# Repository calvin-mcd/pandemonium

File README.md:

# Pandemonium
 
Pandemonium is an alpha staggered ISO pcb with KLE by HaiZeus. It uses an [XIAO nRF52840](https://www.seeedstudio.com/Seeed-XIAO-BLE-nRF52840-p-5201.html) for bluetooth support. The desgin for that is based on [NoahK#1290's](https://kiserdesigns.bigcartel.com/) [Asymptote](https://github.com/KiserDesigns/Asymptote). For a build guide you can mostly refer to the steps from the [Asymptote Guide](https://github.com/KiserDesigns/Asymptote#asymptote-build-guide). Just take extra care with the right orientation of the diodes, as these change quite a bit on this pcb design. The battery cutout is 54mm x 14mm (max width for batteries used is 14mm).

## Layout

[Link](http://www.keyboard-layout-editor.com/#/gists/b0a595a186fab9d96212efed305105f0)

## Cases

1) HaiZeus designed the case to be either used for resin or FDM printing. Use the respective top file for that. 

A universal plate file is included as well as two thick plate options for different bottomrow layouts.  

Hardware needed to assemble the cases is:
- 8x M3x4mm heat set inserts or 8x M3 square nuts (depending on case top printing method) (see reference picture below for the kind of square nuts)
- 8x M3x6mm screws

The bottom has cutouts for SKUF rubber feet available at a couple different online retailers.

2) There is now also a Hull Style Case made by Ty-Fitz for the OG pandenonium pcb.
https://github.com/Ty-Fitz/Pandi-hull

## Firmware

Firmware has been created in zmk by Falconloft. A basic layout to flash the pcb has been provided. The source code is there to edit and create personal layouts for the board.

## Todo

- [X] order & test pcb
- [X] print & test case
- [X] create ZMK firmware

## Disclaimer

This PCB has been fully tested and confirmed to work. The members of the PCB development team are however not liable if you end up with a non-functional pcb. Order at your own risk. Support will not be provided but pull requests will be reviewed and possibly accepted.

## License

This project is released under the GPL v3 License. Please refer to the LICENCE file.

## Credits

Thanks to HaiZeus for the inspiration, KLE and case design.

Many thanks to Falconloft for his work and patience with the firmware.

Big, big thanks to NoahK#1290 for the design inspiration and support. Do check out Noah's work. It is amazing!

And, as always big thanks to the 40s community!

Any questions, contact calvin0563 on Discord.

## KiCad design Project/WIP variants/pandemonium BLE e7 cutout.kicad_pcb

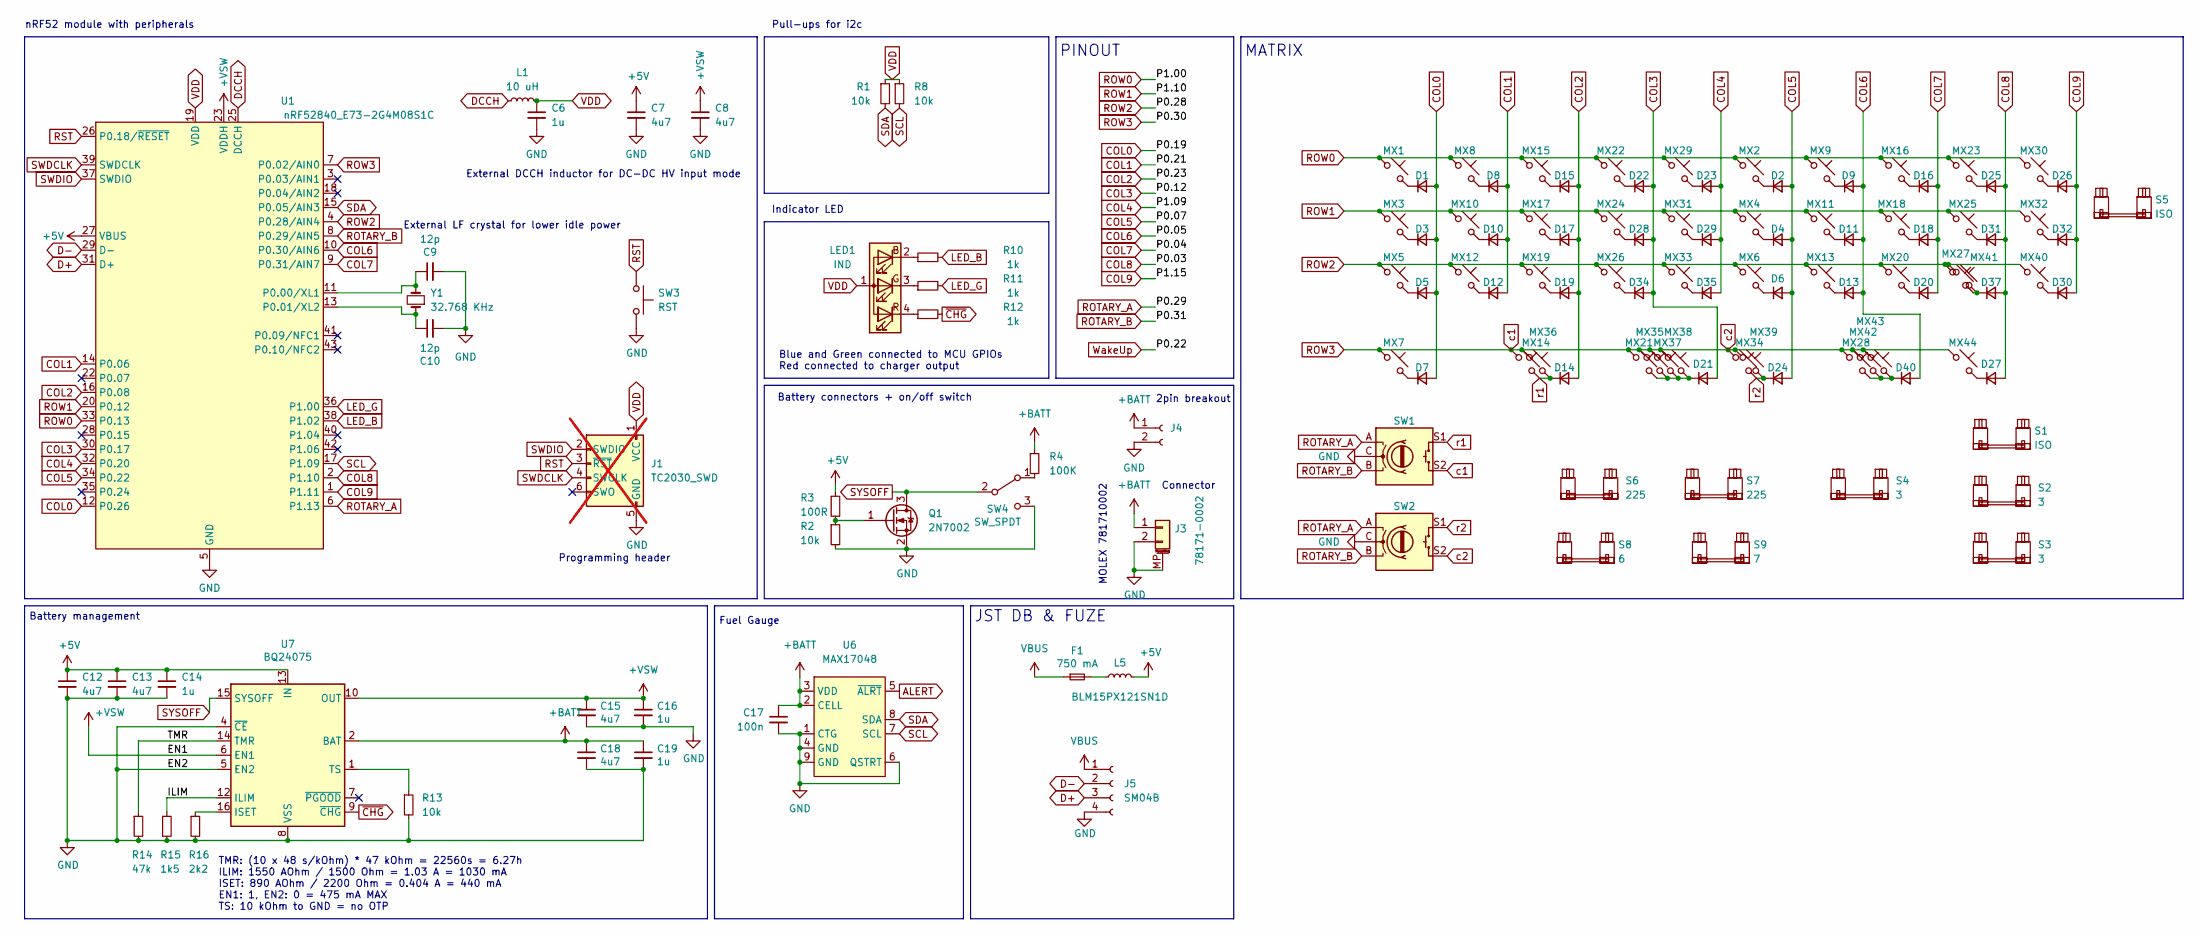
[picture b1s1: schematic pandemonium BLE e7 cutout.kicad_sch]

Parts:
C6, C14, C16, C19: 1u; C_0402_1005Metric; LCSC C52923
C7, C8, C12, C13, C15, C18: 4u7; C_0402_1005Metric; LCSC C23733
C9, C10: 12p; C_0402_1005Metric; LCSC C1547
C17: 100n; C_0402_1005Metric; LCSC C307331
D1, D2, D3, D4, D5, D6, D7, D8, D9, D10, D11, D12, D13, D14, D15, D16, D17, D18, D19, D20, D21, D22, D23, D24, D25, D26, D27, D28, D29, D30, D31, D32, D34, D35, D37, D40: D_Small; D_SOD-123F
F1: 750 mA; Fuse_1206_3216Metric; LCSC C20792
J1: TC2030_SWD; CON_TC2030_outlined; not fitted
J3: 78171-0002; Molex_Pico-EZmate_78171-0002_1x02-1MP_P1.20mm_Vertical; LCSC C505023
J4: Conn_01x02_Female; JST_PH_S2B-PH-K_1x02_P2.00mm_Horizontal
J5: SM04B; JST_SH_SM04B-SRSS-TB_1x04-1MP_P1.00mm_Horizontal
L1: 10 uH; L_0603_1608Metric; LCSC C92982
L5: BLM15PX121SN1D; L_0402_1005Metric; LCSC C88970
LED1: IND; LED_1206R; LCSC C2802677
MX1, MX2, MX3, MX4, MX6, MX8, MX9, MX10, MX11, MX12, MX13, MX14, MX15, MX16, MX17, MX18, MX19, MX20, MX21, MX22, MX23, MX24, MX25, MX26, MX27, MX28, MX29, MX30, MX31, MX32, MX33, MX34, MX35, MX37, MX39, MX42: MX_SW_solder; SW_MX_1u
MX5, MX41: MX_SW_solder; SW_MX_1.5u
MX7, MX36, MX40, MX44: MX_SW_solder; SW_MX_1.25u
MX38, MX43: MX_SW_solder; SW_MX_1.75u
Q1: 2N7002; SOT-23
R1, R8, R13: 10k; R_0402_1005Metric; LCSC C25744
R2: 10k; R_0402_1005Metric
R3: 100R; R_0402_1005Metric
R4: 100K; R_0402_1005Metric
R10, R11, R12: 1k; R_0402_1005Metric; LCSC C11702
R14: 47k; R_0402_1005Metric; LCSC C25792
R15: 1k5; R_0402_1005Metric; LCSC C25867
R16: 2k2; R_0402_1005Metric; LCSC C25879
S1: ISO; STAB_MX_P_ISO
S2, S3, S4: 3; STAB_MX_P_3u
S5: ISO; STAB_MX_P_ISO-ROT
S6, S7: 225; STAB_MX_P_2.25u
S8: 6; STAB_MX_P_6u
S9: 7; STAB_MX_P_7u
SW1, SW2: RotaryEncoder_Switch; ROT_Alps_EC11E-Switch
SW3: RST; SW_T1A2QR; LCSC C100056
SW4: SW_SPDT; SW_MSK12C02-HB
U1: nRF52840_E73-2G4M08S1C; LCSC C356849
U6: MAX17048; DFN-8-1EP_2x2mm_P0.5mm_EP0.8x1.6mm; LCSC C2682616
U7: BQ24075; VQFN-16-1EP_3x3mm_P0.5mm_EP1.6x1.6mm; LCSC C15464
Y1: 32.768 KHz; Crystal_SMD_2012-2Pin_2.0x1.2mm; LCSC C55208

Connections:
+5V: C7.1, C12.1, C13.1, C14.1, R3.1, U1.27 (VBUS), U7.13 (IN); also elsewhere on the board
+BATT: C17.1, C18.1, C19.1, J3.1, J4.1, R4.1, U6.2 (CELL), U6.3 (VDD), U7.2 (BAT), U7.3 (BAT)
+VSW: C8.1, C15.1, C16.1, U1.23 (VDDH), U7.6 (EN1), U7.10 (OUT), U7.11 (OUT)
/ILIM: R15.1, U7.12 (ILIM)
/TMR: R14.1, U7.14 (TMR)
ALERT: U6.5 (~ALRT)
COL0: D1.2 (A), D3.2 (A), D5.2 (A), D7.2 (A), U1.12 (P0.26)
COL1: D8.2 (A), D10.2 (A), D12.2 (A), U1.14 (P0.06)
COL2: D14.2 (A), D15.2 (A), D17.2 (A), D19.2 (A), U1.16 (P0.08)
COL3: D21.2 (A), D22.2 (A), D28.2 (A), D34.2 (A), U1.30 (P0.17)
COL4: D23.2 (A), D29.2 (A), D35.2 (A), U1.32 (P0.20)
COL5: D2.2 (A), D4.2 (A), D6.2 (A), D24.2 (A), U1.34 (P0.22)
COL6: D9.2 (A), D11.2 (A), D13.2 (A), D40.2 (A), U1.10 (P0.30/AIN6)
COL7: D16.2 (A), D18.2 (A), D20.2 (A), U1.9 (P0.31/AIN7)
COL8: D25.2 (A), D27.2 (A), D31.2 (A), D37.2 (A), U1.2 (P1.10)
COL9: D26.2 (A), D30.2 (A), D32.2 (A), U1.1 (P1.11)
D+: J5.3, U1.31 (D+)
D-: J5.2, U1.29 (D-)
DCCH: L1.1, U1.25 (DCCH)
GND: C6.2, C7.2, C8.2, C9.2, C10.2, C12.2, C13.2, C14.2, C15.2, C16.2, C17.2, C18.2, C19.2, J1.5 (GND), J3.2, J3.MP (MountPin), J4.2, J5.4, Q1.2 (S), R2.2, R13.2, R14.2, R15.2, R16.2, SW1.C, SW2.C, SW3.2, SW4.3 (C), U1.5 (GND), U1.21 (GND), U1.24 (GND), U6.1 (CTG), U6.4 (GND), U6.6 (QSTRT), U6.9 (GND), U7.4 (~CE), U7.5 (EN2), U7.8 (VSS), U7.17 (VSS)
LED_B: R10.2, U1.38 (P1.02)
LED_G: R11.2, U1.36 (P1.00)
unnamed: D1.1 (K), MX1.2
unnamed: D2.1 (K), MX2.2
unnamed: D3.1 (K), MX3.2
unnamed: D4.1 (K), MX4.2
unnamed: D5.1 (K), MX5.2
unnamed: D6.1 (K), MX6.2
unnamed: D7.1 (K), MX7.2
unnamed: D8.1 (K), MX8.2
unnamed: D9.1 (K), MX9.2
unnamed: D10.1 (K), MX10.2
unnamed: D11.1 (K), MX11.2
unnamed: D12.1 (K), MX12.2
unnamed: D13.1 (K), MX13.2
unnamed: D15.1 (K), MX15.2
unnamed: D16.1 (K), MX16.2
unnamed: D17.1 (K), MX17.2
unnamed: D18.1 (K), MX18.2
unnamed: D19.1 (K), MX19.2
unnamed: D20.1 (K), MX20.2
unnamed: D21.1 (K), MX21.2, MX35.2, MX37.2, MX38.2
unnamed: D22.1 (K), MX22.2
unnamed: D23.1 (K), MX29.2
unnamed: D25.1 (K), MX23.2
unnamed: D26.1 (K), MX30.2
unnamed: D27.1 (K), MX44.2
unnamed: D28.1 (K), MX24.2
unnamed: D29.1 (K), MX31.2
unnamed: D30.1 (K), MX40.2
unnamed: D31.1 (K), MX25.2
unnamed: D32.1 (K), MX32.2
unnamed: D34.1 (K), MX26.2
unnamed: D35.1 (K), MX33.2
unnamed: D37.1 (K), MX27.2, MX41.2
unnamed: D40.1 (K), MX28.2, MX42.2, MX43.2
unnamed: LED1.2 (BK), R10.1
unnamed: LED1.3 (GK), R11.1
unnamed: LED1.4 (RK), R12.1
unnamed: Q1.1 (G), R2.1, R3.2
unnamed: R4.2, SW4.1 (A)
unnamed: C9.1, U1.11 (P0.00/XL1), Y1.2
unnamed: C10.1, U1.13 (P0.01/XL2), Y1.1
unnamed: R16.1, U7.16 (ISET)
unnamed: R13.1, U7.1 (TS)
ROTARY_A: SW1.A, SW2.A, U1.6 (P1.13)
ROTARY_B: SW1.B, SW2.B, U1.8 (P0.29/AIN5)
ROW0: MX1.1, MX2.1, MX8.1, MX9.1, MX15.1, MX16.1, MX22.1, MX23.1, MX29.1, MX30.1, U1.33 (P0.13)
ROW1: MX3.1, MX4.1, MX10.1, MX11.1, MX17.1, MX18.1, MX24.1, MX25.1, MX31.1, MX32.1, U1.20 (P0.12)
ROW2: MX5.1, MX6.1, MX12.1, MX13.1, MX19.1, MX20.1, MX26.1, MX27.1, MX33.1, MX40.1, MX41.1, U1.4 (P0.28/AIN4)
ROW3: MX7.1, MX14.1, MX21.1, MX28.1, MX34.1, MX35.1, MX36.1, MX37.1, MX38.1, MX39.1, MX42.1, MX43.1, MX44.1, SW1.S2, SW2.S2, U1.7 (P0.02/AIN0)
RST: J1.3 (~RST), SW3.1, U1.26 (P0.18/~RESET)
SCL: R8.2, U1.17 (P1.09), U6.7 (SCL)
SDA: R1.2, U1.15 (P0.05/AIN3), U6.8 (SDA)
SWDCLK: J1.4 (SWCLK), U1.39 (SWDCLK)
SWDIO: J1.2 (SWDIO), U1.37 (SWDIO)
SYSOFF: Q1.3 (D), SW4.2 (B), U7.15 (SYSOFF)
VBUS: J5.1; also elsewhere on the board
VDD: C6.1, J1.1 (VCC), L1.2, LED1.1 (A), R1.1, R8.1, U1.19 (VDD)
r1: D14.1 (K), MX14.2, MX36.2, SW1.S1
r2: D24.1 (K), MX34.2, MX39.2, SW2.S1
~CHG: R12.2, U7.9 (~CHG)

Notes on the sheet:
Programming header
Pull-ups for i2c
Indicator LED
Blue and Green connected to MCU GPIOs Red connected to charger output
MOLEX 781710002
nRF52 module with peripherals
Connector
TMR: (10 x 48 s/kOhm) * 47 kOhm = 22560s = 6.27h ILIM: 1550 AOhm / 1500 Ohm = 1.03 A = 1030 mA ISET: 890 AOhm / 2200 Ohm = 0.404 A = 440 mA EN1: 1, EN2: 0 = 475 mA MAX TS: 10 kOhm to GND = no OTP
Battery management
PINOUT
Battery connectors + on/off switch
MATRIX
External LF crystal for lower idle power
External DCCH inductor for DC-DC HV input mode
JST DB & FUZE
2pin breakout
Fuel Gauge

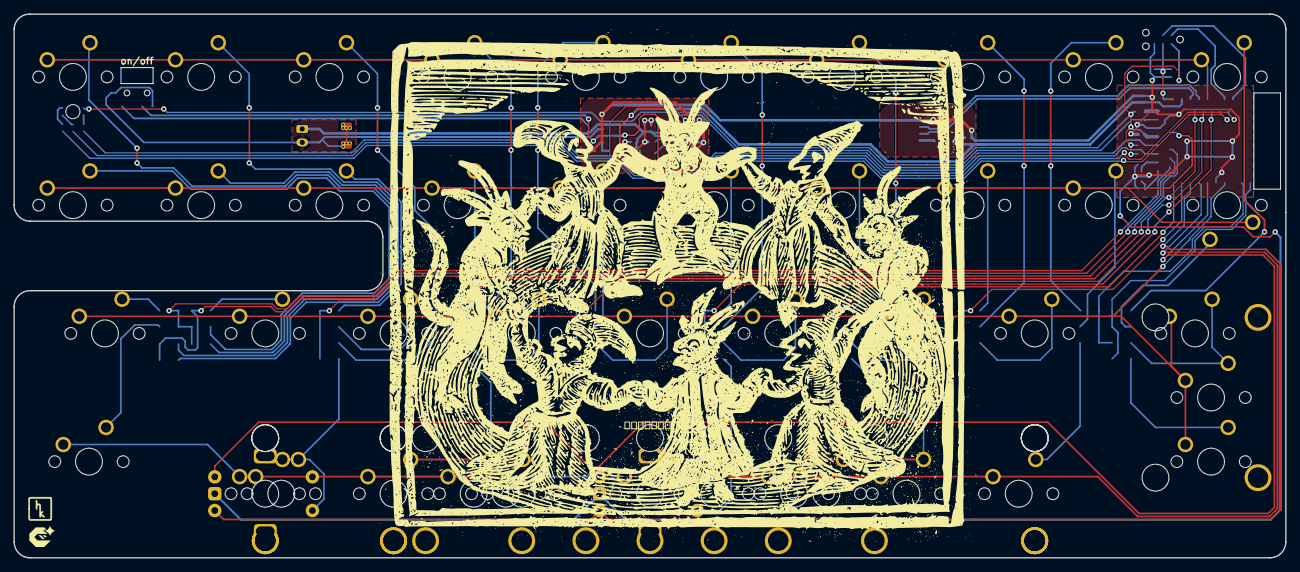
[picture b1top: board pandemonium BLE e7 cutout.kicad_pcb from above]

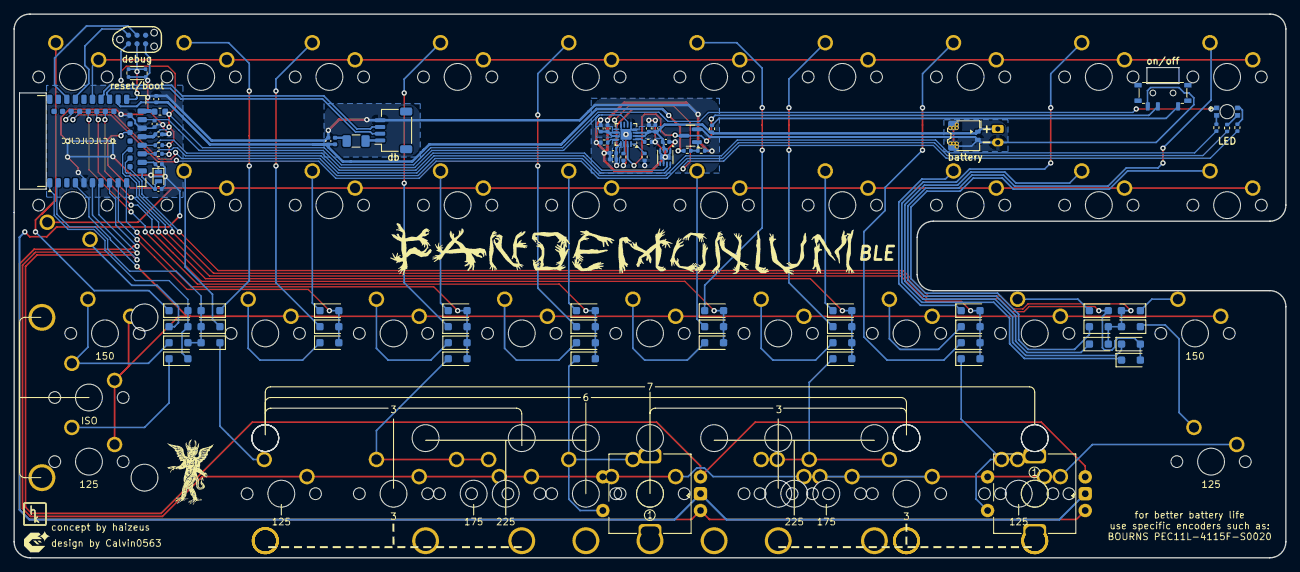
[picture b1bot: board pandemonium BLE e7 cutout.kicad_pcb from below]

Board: 2 copper layers, 188.9 x 80.8 mm, 130 parts (76 on the bottom side), 82 nets.

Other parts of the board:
F2: 750 mA; Fuse_1206_3216Metric
L2: BLM15PX121SN1D; L_0402_1005Metric

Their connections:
+5V: L2.2; also elsewhere on the board
unnamed: F2.2, L2.1
VBUS: F2.1; also elsewhere on the board

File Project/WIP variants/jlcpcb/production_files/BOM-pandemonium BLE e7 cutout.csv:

Comment,Designator,Footprint,LCSC,Quantity
RST,SW3,SW_T1A2QR,C100056,1
1k,"R10,R11,R12",R_0402_1005Metric,C11702,3
BQ24075,U7,VQFN-16-1EP_3x3mm_P0.5mm_EP1.6x1.6mm,C15464,1
12p,"C10,C9",C_0402_1005Metric,C1547,2
SM04B,J5,JST_SH_SM04B-SRSS-TB_1x04-1MP_P1.00mm_Horizontal,C160404,1
750 mA,F2,Fuse_1206_3216Metric,C20792,1
4u7,"C12,C13,C15,C18,C7,C8",C_0402_1005Metric,C23733,6
100R,R3,R_0402_1005Metric,C25076,1
100K,R4,R_0402_1005Metric,C25530,1
10k,"R1,R13,R2,R8",R_0402_1005Metric,C25744,4
47k,R14,R_0402_1005Metric,C25792,1
1k5,R15,R_0402_1005Metric,C25867,1
2k2,R16,R_0402_1005Metric,C25879,1
MAX17048,U6,DFN-8-1EP_2x2mm_P0.5mm_EP0.8x1.6mm,C2682616,1
IND,LED1,LED_1206R,C2802677,1
100n,C17,C_0402_1005Metric,C307331,1
nRF52840_E73-2G4M08S1C,U1,nRF52840_E73-2G4M08S1C,C356849,1
SW_SPDT,SW4,SW_MSK12C02-HB,C431540,1
78171-0002,J3,Molex_Pico-EZmate_78171-0002_1x02-1MP_P1.20mm_Vertical,C505023,1
1u,"C14,C16,C19,C6",C_0402_1005Metric,C52923,4
32.768 KHz,Y1,Crystal_SMD_2012-2Pin_2.0x1.2mm,C55208,1
D_Small,"D1,D10,D11,D12,D13,D14,D15,D16,D17,D18,D19,D2,D20,D21,D22,D23,D24,D25,D26,D27,D28,D29,D3,D30,D31,D32,D34,D35,D37,D4,D40,D5,D6,D7,D8,D9",D_SOD-123F,C81598,36
2N7002,Q1,SOT-23,C8545,1
BLM15PX121SN1D,L2,L_0402_1005Metric,C88970,1
10 uH,L1,L_0603_1608Metric,C92982,1

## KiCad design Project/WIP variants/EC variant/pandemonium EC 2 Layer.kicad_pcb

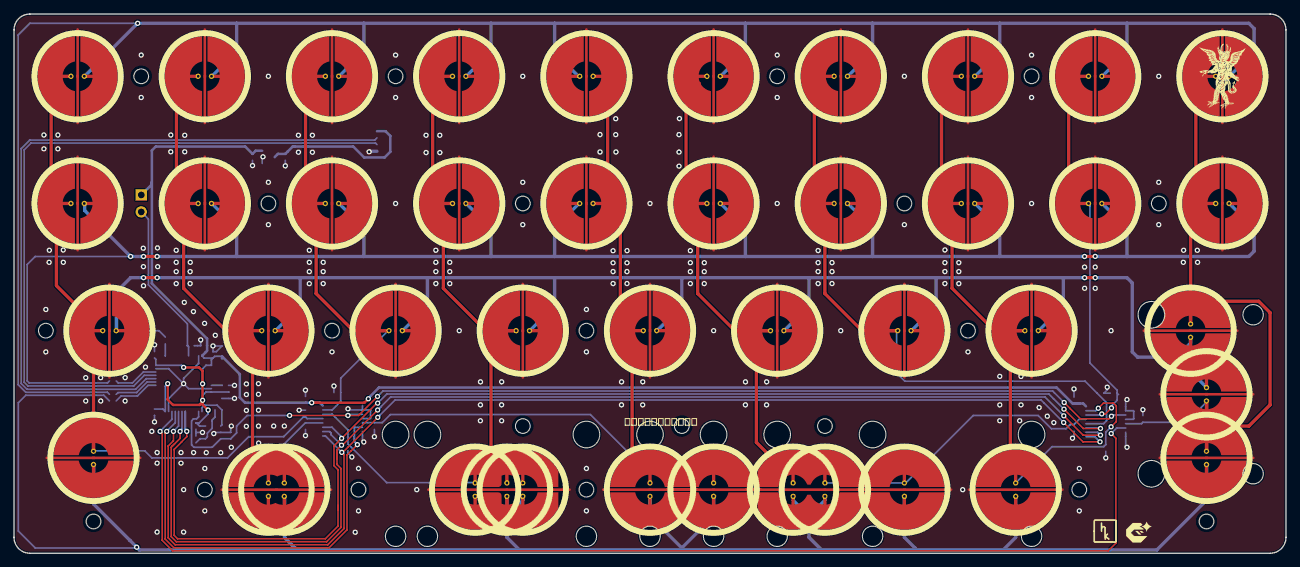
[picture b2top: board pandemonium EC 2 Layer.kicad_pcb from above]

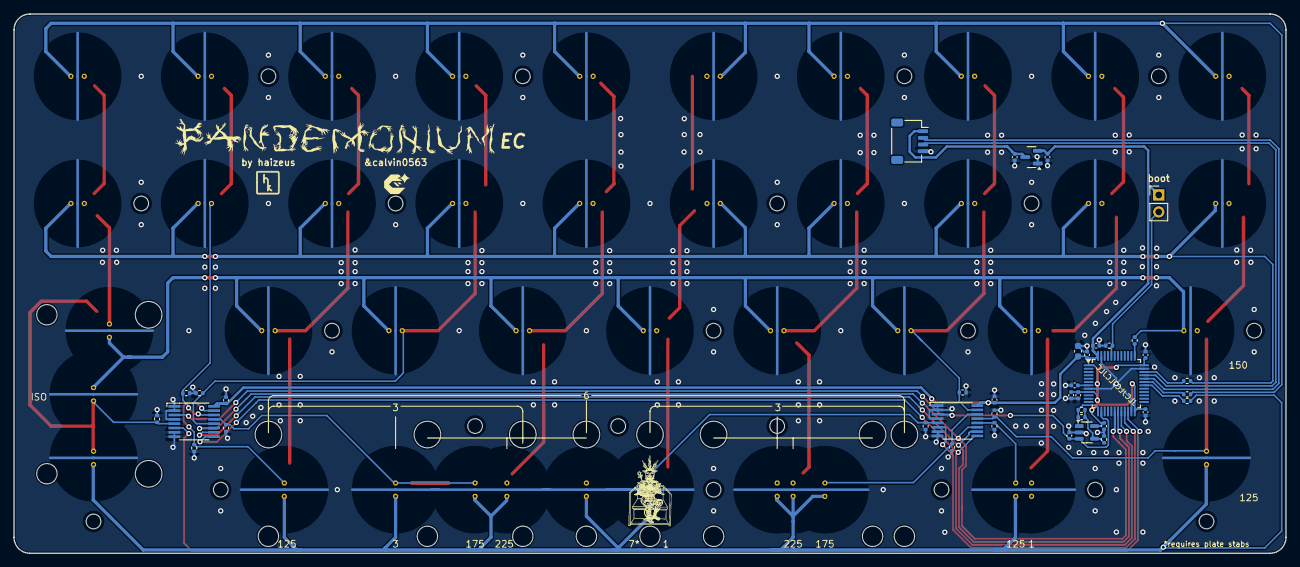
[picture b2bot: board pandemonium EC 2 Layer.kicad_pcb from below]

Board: 2 copper layers, 190.5 x 80.8 mm, 104 parts (39 on the bottom side), 33 nets.

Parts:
C29, C31, C32, C38: 100n; C_0402_1005Metric
C30: 220pF NP0; C_0402_1005Metric
C33, C34, C35, C36, C40: 100nF; C_0402_1005Metric
C37: 10uF; C_0603_1608Metric
C39: 1u; C_0402_1005Metric
C41, C42: 1uF; C_0402_1005Metric
H1, H2, H3, H4, H5, H6, H7, H8, H9, H10, H11, H12, H14, H15, H16, H17, H18, H19, H20, H23, H24: MountingHole; HOLE_M2 (no arrow)
J2: SM04B; JST_SH_SM04B-SRSS-TB_1x04-1MP_P1.00mm_Horizontal
R1, R2, R3, R4: 100; R_0402_1005Metric
R13, R16, R17, R18, R19, R21, R24, R25, R26, R27, R28: 100k; R_0402_1005Metric
R14: 1k; R_0402_1005Metric
R15: DNP; R_0402_1005Metric
R20: 10k; R_0402_1005Metric
S1, S2: 225; STAB_MX_2.25u
S3: 225; STAB_MX_ISO-ROT
S4, S5: 3; STAB_MX_3u
SW1: DFU; PinHeader_1x02_P2.54mm_Vertical
SW_EC1, SW_EC2, SW_EC3, SW_EC4, SW_EC5, SW_EC6, SW_EC7, SW_EC8, SW_EC9, SW_EC10, SW_EC11, SW_EC12, SW_EC13, SW_EC14, SW_EC15, SW_EC16, SW_EC17, SW_EC18, SW_EC19, SW_EC20, SW_EC21, SW_EC22, SW_EC23, SW_EC24, SW_EC25, SW_EC26, SW_EC27, SW_EC28, SW_EC29, SW_EC30, SW_EC31, SW_EC35, SW_EC38, SW_EC39, SW_EC40: Topre; ecs_pad_1U_no_ring
SW_EC32: Topre; ecs_pad_no_ring_1u&1.25u&1.5u
SW_EC33: Topre; ecs_pad_0.25U_0.125U_spaced_no_ring_cut_right
SW_EC34: Topre; ecs_pad_1U_no_ring_1u_edge_cut_horizontal
SW_EC36: Topre; ecs_pad_no_ring_stepped&normal_cut
U5: OPA354; SOT-23-5
U6, U7: 74HC4051; TSSOP16
U8: STM32F072CBT6; LQFP-48_7x7mm_P0.5mm
U9: XC6206PxxxMR-Regulator_Linear; SOT-23

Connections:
+3V3: C29.2, C31.2, C32.2, C33.1, C34.1, C35.1, C36.1, C37.1, C38.1, C39.1, C42.2, SW1.1, U5.5 (V+), U6.16 (VCC), U7.16 (VCC), U8.1 (VBAT), U8.9 (VDDA), U8.24 (VDD), U8.36 (VDDIO2), U8.48 (VDD), U9.2 (VO)
+5V: C41.2, J2.1, U9.3 (VI)
ADC: R13.1, R15.1, U5.1, U8.13 (PA3)
AMUX_SEL_0: U6.11 (S0), U7.11 (S0), U8.18 (PB0)
AMUX_SEL_1: U6.10 (S1), U7.10 (S1), U8.19 (PB1)
AMUX_SEL_2: U6.9 (S2), U7.9 (S2), U8.20 (PB2)
APLEX_EN_PIN_0: U6.6 (~E), U8.21 (PB10)
APLEX_EN_PIN_1: U7.6 (~E), U8.22 (PB11)
APLEX_OUT: C30.1, U5.3 (+), U6.3 (A), U7.3 (A), U8.14 (PA4)
BOOT0: R20.1, SW1.2, U8.44 (BOOT0)
COL0: R16.1, SW_EC1.1, SW_EC11.1, SW_EC21.1, SW_EC31.1, U6.13 (A0)
COL1: R19.1, SW_EC2.1, SW_EC12.1, SW_EC22.1, SW_EC32.1, U6.12 (A3)
COL2: R18.1, SW_EC3.1, SW_EC13.1, SW_EC23.1, U6.15 (A2)
COL3: R17.1, SW_EC4.1, SW_EC14.1, SW_EC24.1, SW_EC33.1, U6.14 (A1)
COL4: R21.1, SW_EC5.1, SW_EC15.1, SW_EC25.1, SW_EC34.1, SW_EC35.1, U6.5 (A5)
COL5: R24.1, SW_EC6.1, SW_EC16.1, SW_EC26.1, SW_EC36.1, SW_EC40.1, U7.13 (A0)
COL6: R27.1, SW_EC7.1, SW_EC17.1, SW_EC27.1, U7.12 (A3)
COL7: R26.1, SW_EC8.1, SW_EC18.1, SW_EC28.1, SW_EC38.1, U7.15 (A2)
COL8: R25.1, SW_EC9.1, SW_EC19.1, U7.14 (A1)
COL9: R28.1, SW_EC10.1, SW_EC20.1, SW_EC29.1, SW_EC30.1, SW_EC39.1, U7.5 (A5)
D_N: J2.2, U8.32 (PA11)
D_P: J2.3, U8.33 (PA12)
GND: C29.1, C30.2, C31.1, C32.1, C33.2, C34.2, C35.2, C36.2, C37.2, C38.2, C39.2, C40.2, C41.1, C42.1, J2.4, R14.2, R16.2, R17.2, R18.2, R19.2, R20.2, R21.2, R24.2, R25.2, R26.2, R27.2, R28.2, SW_EC1.3 (SG), SW_EC2.3 (SG), SW_EC3.3 (SG), SW_EC4.3 (SG), SW_EC5.3 (SG), SW_EC6.3 (SG), SW_EC7.3 (SG), SW_EC8.3 (SG), SW_EC9.3 (SG), SW_EC10.3 (SG), SW_EC11.3 (SG), SW_EC12.3 (SG), SW_EC13.3 (SG), SW_EC14.3 (SG), SW_EC15.3 (SG), SW_EC16.3 (SG), SW_EC17.3 (SG), SW_EC18.3 (SG), SW_EC19.3 (SG), SW_EC20.3 (SG), SW_EC21.3 (SG), SW_EC22.3 (SG), SW_EC23.3 (SG), SW_EC24.3 (SG), SW_EC25.3 (SG), SW_EC26.3 (SG), SW_EC27.3 (SG), SW_EC28.3 (SG), SW_EC29.3 (SG), SW_EC30.3 (SG), SW_EC31.3 (SG), SW_EC32.3 (SG), SW_EC33.3 (SG), SW_EC34.3 (SG), SW_EC35.3 (SG), SW_EC36.3 (SG), SW_EC38.3 (SG), SW_EC39.3 (SG), SW_EC40.3 (SG), U5.2 (V-), U6.1 (A4), U6.2 (A6), U6.4 (A7), U6.7 (VEE), U6.8 (GND), U7.1 (A4), U7.2 (A6), U7.4 (A7), U7.7 (VEE), U7.8 (GND), U8.8 (VSSA), U8.23 (VSS), U8.35 (VSS), U8.47 (VSS), U9.1 (GND)
NRST: C40.1, U8.7 (NRST)
unnamed: R13.2, R14.1, R15.2, U5.4 (-)
unnamed: R4.1, U8.30 (PA9)
unnamed: R1.1, U8.31 (PA10)
unnamed: R2.1, U8.34 (PA13)
unnamed: R3.1, U8.37 (PA14)
ROW0: R1.2, SW_EC1.2, SW_EC2.2, SW_EC3.2, SW_EC4.2, SW_EC5.2, SW_EC6.2, SW_EC7.2, SW_EC8.2, SW_EC9.2, SW_EC10.2
ROW1: R2.2, SW_EC11.2, SW_EC12.2, SW_EC13.2, SW_EC14.2, SW_EC15.2, SW_EC16.2, SW_EC17.2, SW_EC18.2, SW_EC19.2, SW_EC20.2
ROW2: R3.2, SW_EC21.2, SW_EC22.2, SW_EC23.2, SW_EC24.2, SW_EC25.2, SW_EC26.2, SW_EC27.2, SW_EC28.2, SW_EC29.2, SW_EC30.2
ROW3: R4.2, SW_EC31.2, SW_EC32.2, SW_EC33.2, SW_EC34.2, SW_EC35.2, SW_EC36.2, SW_EC38.2, SW_EC39.2, SW_EC40.2

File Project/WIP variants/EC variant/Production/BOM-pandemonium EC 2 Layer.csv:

Comment,Designator,Footprint,LCSC,Quantity
1k,R14,R_0402_1005Metric,C11702,1
220pF NP0,C30,C_0402_1005Metric,C1530,1
SM04B,J2,JST_SH_SM04B-SRSS-TB_1x04-1MP_P1.00mm_Horizontal,C160404,1
10uF,C37,C_0603_1608Metric,C1691,1
100,"R1,R2,R3,R4",R_0402_1005Metric,C25076,4
10k,R20,R_0402_1005Metric,C25531,1
100k,"R13,R16,R17,R18,R19,R21,R24,R25,R26,R27,R28",R_0402_1005Metric,C25741,11
100n,"C29,C31,C32,C33,C34,C35,C36,C38,C40",C_0402_1005Metric,C307331,9
OPA354,U5,SOT-23-5,C36384,1
1u,"C39,C41,C42",C_0402_1005Metric,C52923,3
XC6206PxxxMR-Regulator_Linear,U9,SOT-23,C5446,1
74HC4051,"U6,U7",TSSOP16,C5645,2
STM32F072CBT6,U8,LQFP-48_7x7mm_P0.5mm,C81720,1

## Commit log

2023-06-07 initialise
2023-06-28 backup
2023-07-10 step file, gerber files created
2023-07-10 production zip
2023-08-20 added images of Haizeus' case design
2023-10-18 updated firmware, still work in progress
2023-10-23 added latest case file, firmware files, updated readme
2023-10-29 updated readme with battery info
2023-11-09 BLE progress
2023-11-17 EC version finished
2023-12-02 separeted EC project from the OG and BLE-wip
2024-01-04 small work on pandi EC and BLE
2024-01-09 switching to holyiot for BLE
2024-01-19 EC plates created
2024-02-09 BLE version close to proto run
    implement john's last suggestions
2024-02-11 changes to topre version and BLE version
2024-02-13 update readme with hull case
2024-02-27 fresh gerbers, easier THT labelling
2024-02-27 fresh gerbers
2024-03-30 project cleanup, WIP folder
2024-09-16 e73 version work
2024-10-18 firmware fix
2024-12-24 integrated wip
2024-12-31 feedback
2025-01-24 battery charging sysoff added
2025-01-29 small changes
    added rotary disclaimer
2025-03-01 ble integrated wip
2025-03-23 production files EC
2025-05-03 EC 2 layer production files
2025-05-06 BLE & EC edited
    requires production files!!
2025-05-09 jst revision
    fresh production files
